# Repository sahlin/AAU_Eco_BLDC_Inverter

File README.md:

# AAU_Eco_BLDC_Inverter
Aalborg University BLDC control system for Shell EcoMarathon

This hardware achieved a second place in the efficiency competition Shell Ecomarathon Europe 2019 on a special designed hydrogen fueled eco racer car. The car was built by students at Aalborg University - Department of Energy Technology. We achieved a result of 214.27 km/m3 H2 (which is about 620 km/l 95 octane equivalent) and the motor system was a Grundfos PMSM motor and is rated at 2000 RPM, 2 Nm, 10.8V og 38A , but we are pushing it to 60A and 2500 RPM!

It's effectiveness with inverter included is best at 2000+ RPM and >1 Nm (90%), which put it at for our entire run (except for acceleration).

The initial work was done by the VESC Project. https://vesc-project.com/

Hardware is licensed under the Creative Commons Attribution-ShareAlike 4.0 International License. To view a copy of this license, visit http://creativecommons.org/licenses/by-sa/4.0/.

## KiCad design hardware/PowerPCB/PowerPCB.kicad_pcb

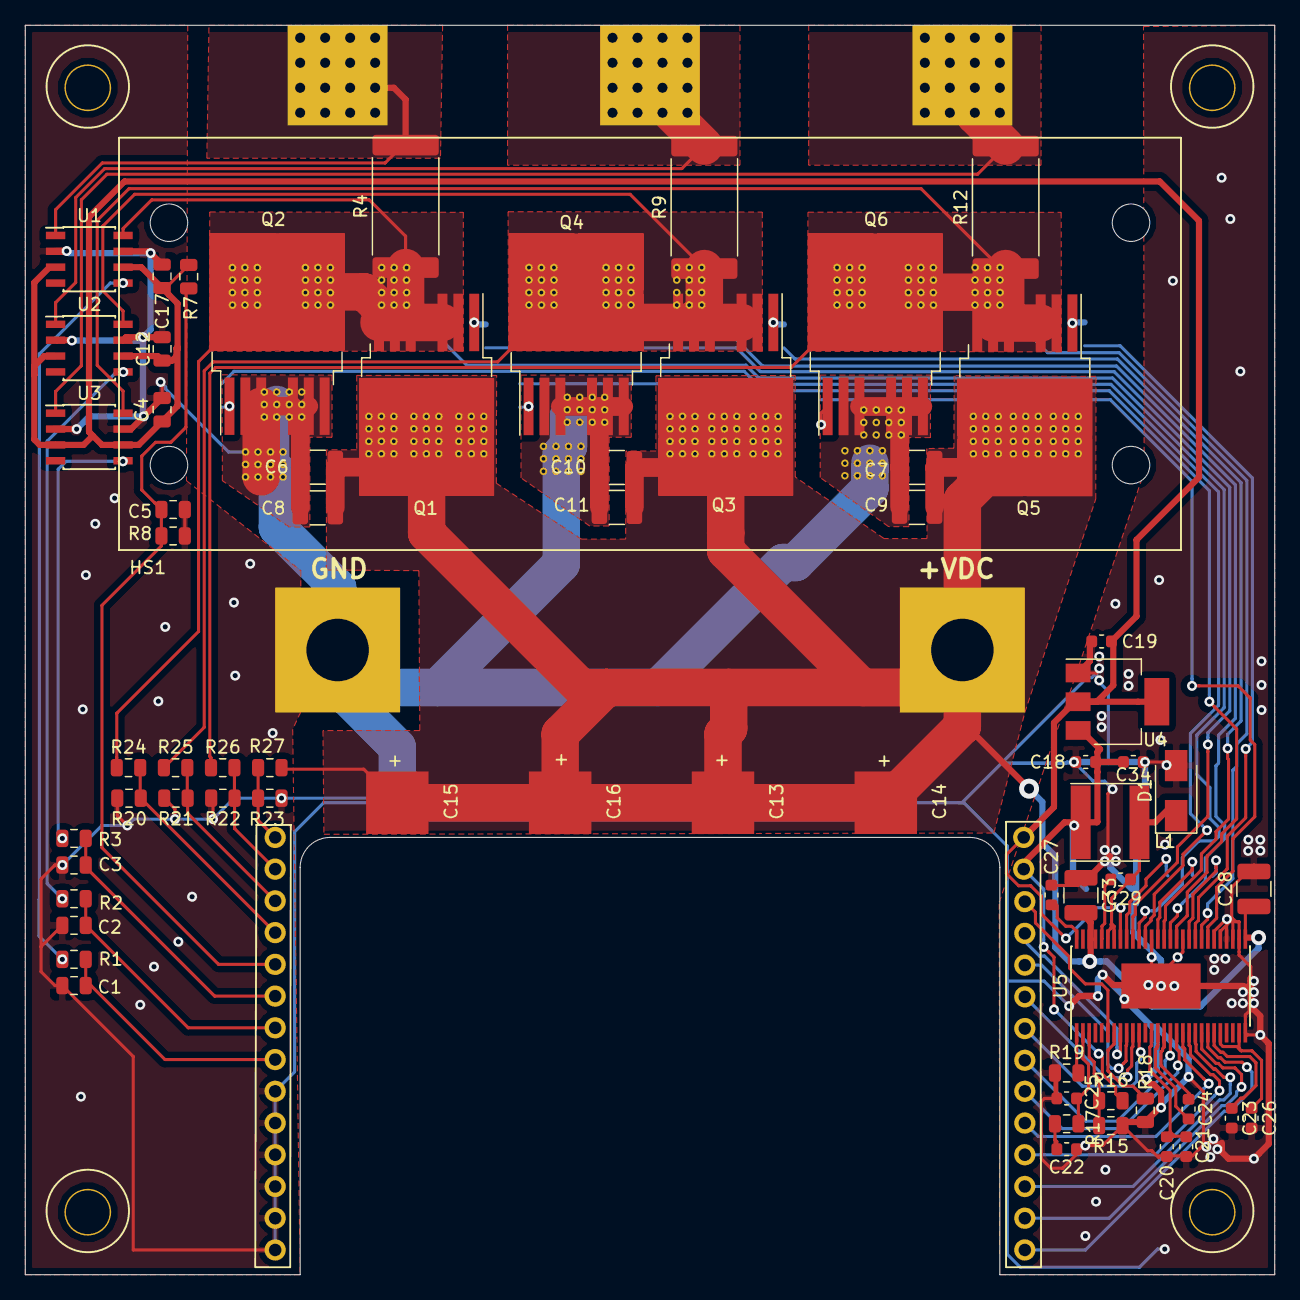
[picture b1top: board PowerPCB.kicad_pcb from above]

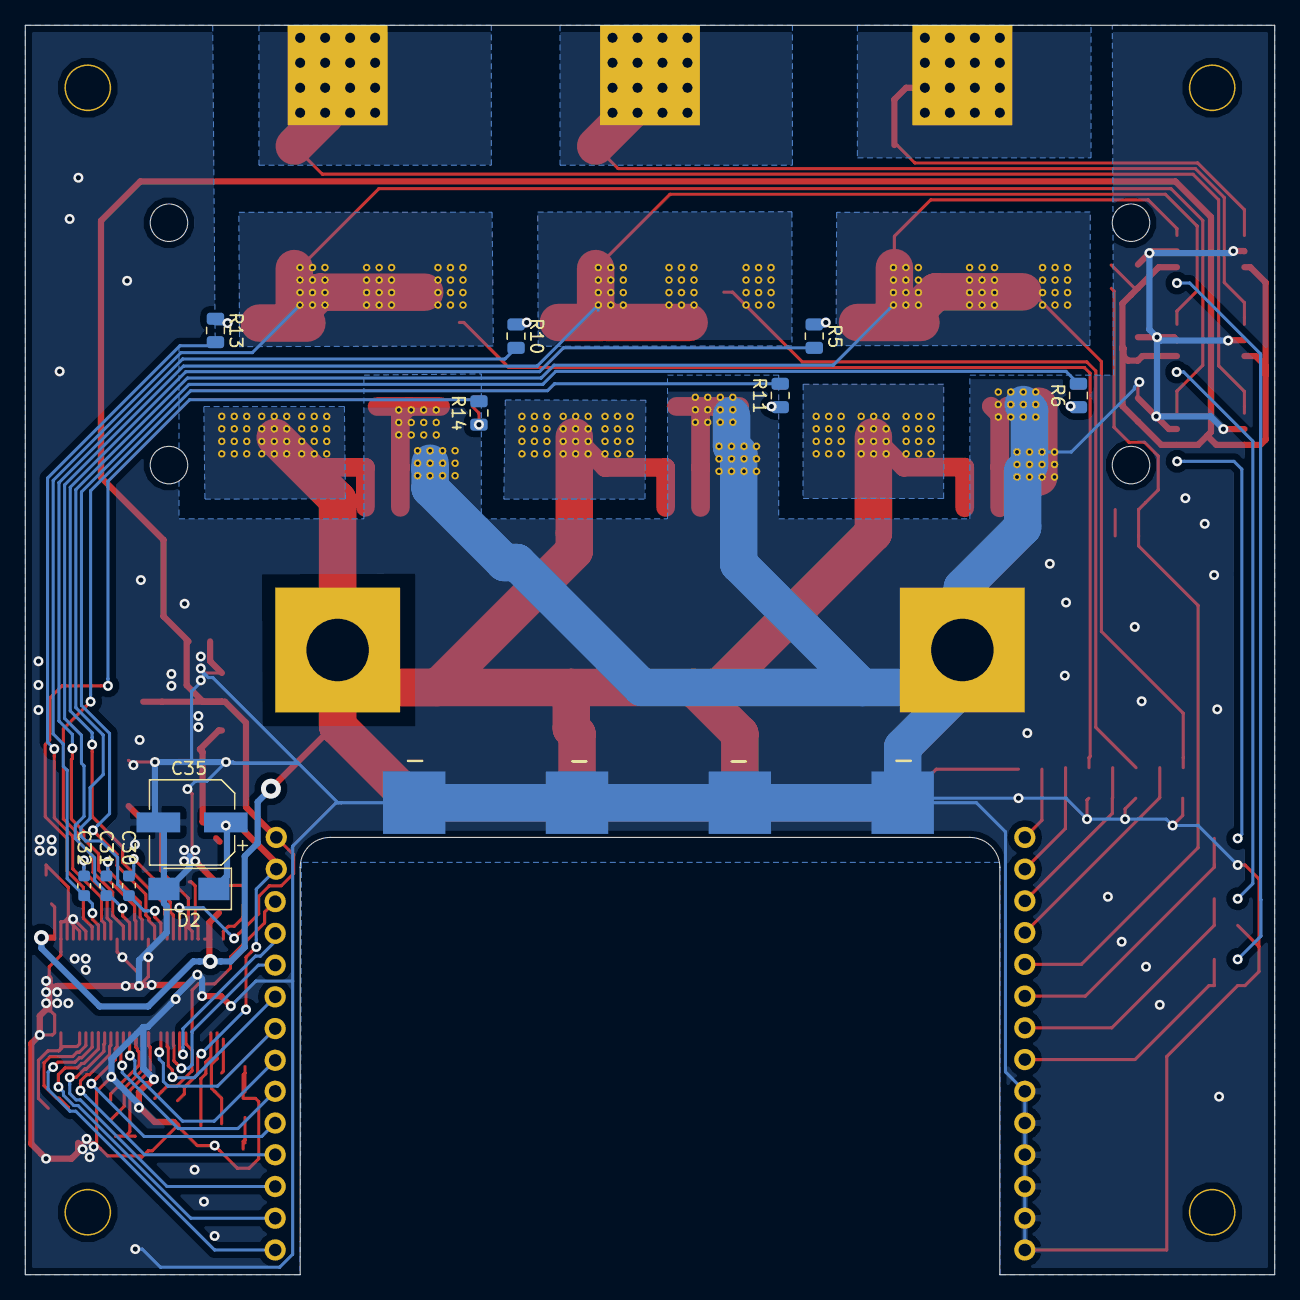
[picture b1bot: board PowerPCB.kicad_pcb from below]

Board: 2 copper layers, 100.0 x 100.0 mm, 111 parts (11 on the bottom side), 61 nets.

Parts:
C1, C2, C3: 4.7nF; C_0805_2012Metric
C4, C12, C17: 100nF; C_0805_2012Metric
C5: 2.2uF; C_0805_2012Metric
C6, C7, C8, C9, C10, C11, C28, C33: 4.7uF 100V; C_1210_3225Metric
C13, C14, C15, C16: EEUFC1J681L; CAP_inverter
C18, C19, C29: 100nF; C_0603_1608Metric
C20, C21, C23, C26, C34: 2.2uF; C_0603_1608Metric
C22: 6.8nF; C_0603_1608Metric
C24: 22nF; C_0603_1608Metric
C25: 120pF; C_0603_1608Metric
C27: 15nF; C_0603_1608Metric
C30, C31, C32: 220nF; C_0603_1608Metric
C35: 68uF; CP_Elec_6.3x5.7
D1: B360A-13-F; D_SMA
D2: SMAJ5.0A; D_SMA
HS1: Heatsink; HeatSink
J1: InverterConn
J2: PH_A; BulletConnector
J3: VDC; 5mmWireConn
J4: PH_B; BulletConnector
J5: PH_C; BulletConnector
J6: GND; 5mmWireConn
J7, J8, J9, J10: Conn_01x01; Spacer
L1: L; L_Taiyo-Yuden_NR-60xx
Q1, Q2, Q3, Q4, Q5, Q6: IPB010N06N; TO-263-6
R1, R2, R3: 100; R_0805_2012Metric
R4, R9, R12: Shunt 0.0002; R_4020_10251Metric_Pad1.65x5.30mm_HandSolder
R5, R6, R10, R11, R13, R14: 6.8; R_0805_2012Metric
R7: 10k NTC; R_0805_2012Metric
R8, R18: 10k; R_0805_2012Metric
R15: 3.3k; R_0805_2012Metric
R16: 18k; R_0805_2012Metric
R17: 15k; R_0805_2012Metric
R19: 220k; R_0805_2012Metric
R20, R21, R22, R23: 2.2k; R_0805_2012Metric
R24, R25, R26, R27: 39k; R_0805_2012Metric
U1, U2, U3: INA282; SOIC-8_3.9x4.9mm_P1.27mm
U4: TS1117BCW33; SOT-223-3_TabPin2
U5: DRV8301; HTSSOP-56-1EP_6.1x14mm_P0.5mm_EP3.61x6.35mm
Via1, Via2, Via3, Via4, Via5, Via6, Via7, Via8, Via9, Via10, Via11, Via12, Via13, Via14, Via15, Via16, Via17, Via18, Via19, Via20, Via21, Via22, Via23, Via24: Via_array

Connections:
+5V: C18.1, C34.1, C35.1, D2.1, J1.27, L1.1, R16.2, U4.3
+VDC: C6.2, C7.1, C8.1, C9.1, C10.1, C11.1, C13.1, C14.1, C15.1, C16.1, C28.1, C33.2, J3.1, Q1.D, Q3.D, Q5.D, R27.1, U5.29, U5.53, U5.54, Via13.1, Via14.1, Via15.1, Via16.1, Via17.1, Via18.1, Via19.1, Via20.1, Via21.1
/CS: J1.25, U5.8
/CURR_A: C1.1, J1.8, R1.2
/CURR_B: C2.1, J1.7, R2.2
/CURR_C: C3.1, J1.6, R3.2
/DRV8301/AVDD: C26.1, U5.24, U5.27
/DRV8301/BST_BK: C29.2, U5.52
/DRV8301/COMP: C25.2, R17.2, U5.2
/DRV8301/CP1: C24.1, U5.14
/DRV8301/CP2: C24.2, U5.15
/DRV8301/DTC: R18.1, U5.7
/DRV8301/DVDD: C23.1, U5.23
/DRV8301/GH_A: R5.2, U5.47
/DRV8301/GH_B: R10.2, U5.42
/DRV8301/GH_C: R13.2, U5.37
/DRV8301/GL_A: R6.2, U5.45
/DRV8301/GL_B: R11.2, U5.40
/DRV8301/GL_C: R14.2, U5.35
/DRV8301/GVDD: C20.2, C21.2, U5.13
/DRV8301/PH: C29.1, D1.1, L1.2, U5.50, U5.51
/DRV8301/RT_CLK: R19.2, U5.1
/DRV8301/SH_A: C30.1, Q1.S, Q2.D, R4.1, R24.1, U1.8, U5.46, Via1.1, Via2.1, Via3.1
/DRV8301/SH_B: C31.1, Q3.S, Q4.D, R9.1, R25.1, U2.8, U5.41, Via5.1, Via6.1, Via7.1
/DRV8301/SH_C: C32.1, Q5.S, Q6.D, R12.1, R26.1, U3.8, U5.36, Via9.1, Via10.1, Via11.1
/DRV8301/VSENSE: R15.2, R16.1, U5.3
/EN_GATE: J1.21, U5.16
/FAULT: J1.26, U5.6
/INH_A: J1.20, U5.17
/INH_B: J1.18, U5.19
/INH_C: J1.16, U5.21
/INL_A: J1.19, U5.18
/INL_B: J1.17, U5.20
/INL_C: J1.15, U5.22
/Inverter/C_A: R1.1, U1.5
/Inverter/C_B: R2.1, U2.5
/Inverter/C_C: R3.1, U3.5
/SCLK: J1.22, U5.11
/SDI: J1.24, U5.9
/SDO: J1.23, U5.10
/SENS_A: J1.4, R20.1, R24.2
/SENS_B: J1.3, R21.1, R25.2
/SENS_C: J1.2, R22.1, R26.2
/SENS_SUPPLY: J1.1, R23.1, R27.2
/TEMP: C5.1, J1.5, R7.2, R8.1
GND: C1.2, C2.2, C3.2, C4.2, C5.2, C6.1, C7.2, C8.2, C9.2, C10.2, C11.2, C12.2, C13.2, C14.2, C15.2, C16.2, C17.2, C18.2, C19.2, C20.1, C21.1, C22.1, C23.2, C25.1, C26.2, C27.1, C28.2, C33.1, C34.2, C35.2, D1.2, D2.2, J1.9, J1.10, J1.11, J1.12, J1.13, J1.14, J6.1, Q2.S, Q4.S, Q6.S, R8.2, R15.1, R18.2, R19.1, R20.2, R21.2, R22.2, R23.2, U1.2, U1.7, U2.2, U2.7, U3.2, U3.7, U4.1, U5.28, U5.30, U5.31, U5.32, U5.33, U5.34, U5.39, U5.44, U5.57, Via4.1, Via8.1, Via12.1, Via22.1, Via23.1, Via24.1
unnamed: C22.2, R17.1
unnamed: C27.2, U5.56
unnamed: C30.2, U5.48
unnamed: C31.2, U5.43
unnamed: C32.2, U5.38
unnamed: J2.1, R4.2, U1.1
unnamed: J4.1, R9.2, U2.1
unnamed: J5.1, R12.2, U3.1
unnamed: Q1.G, R5.1
unnamed: Q2.G, R6.1
unnamed: Q3.G, R10.1
unnamed: Q4.G, R11.1
unnamed: Q5.G, R13.1
unnamed: Q6.G, R14.1
VCC: C4.1, C12.1, C17.1, C19.1, J1.28, R7.1, U1.3, U1.6, U2.3, U2.6, U3.3, U3.6, U4.2, U5.49

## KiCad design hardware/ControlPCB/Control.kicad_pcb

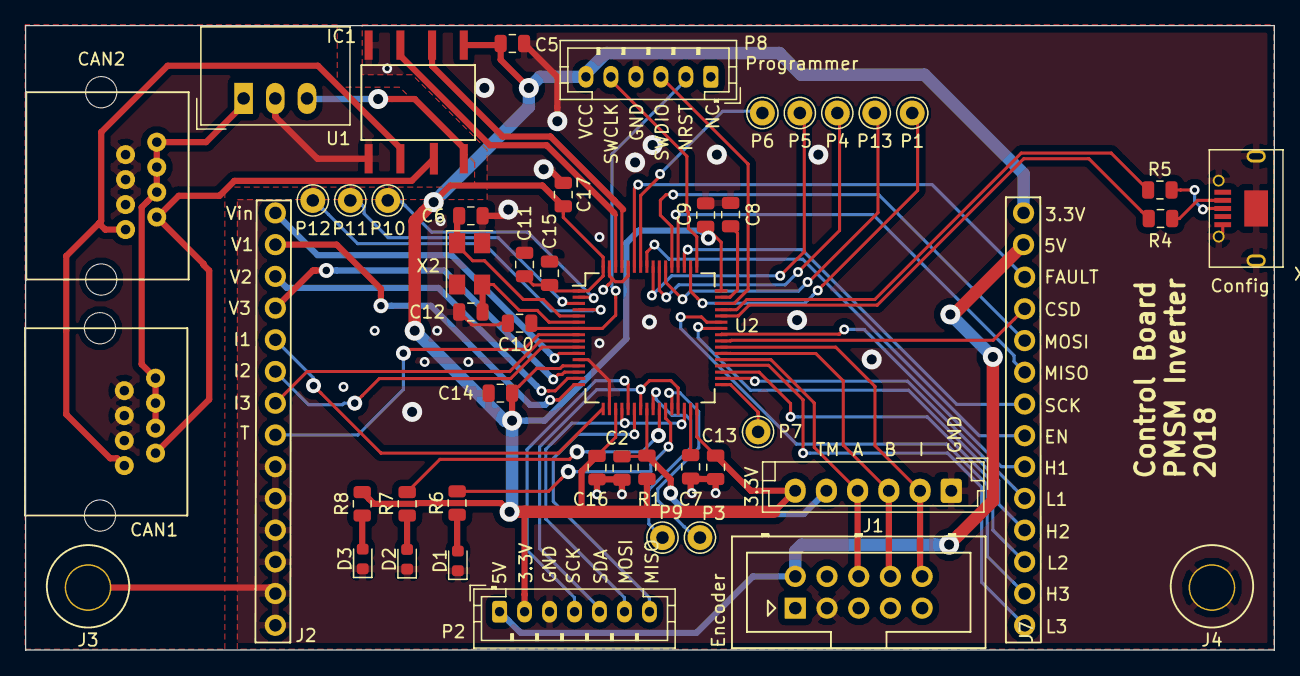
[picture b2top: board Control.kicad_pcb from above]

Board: 2 copper layers, 100.0 x 50.0 mm, 48 parts (0 on the bottom side), 65 nets.

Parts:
C2, C10: 100n; C_0805_2012Metric
C5, C7, C8, C9, C11, C13, C14, C15, C16, C17: 2.2u; C_0805_2012Metric
C6, C12: 15p; C_0805_2012Metric
CAN1, CAN2: RJ45CAN; RJ45
D1: RED; LED_0603_1608Metric
D2: GREEN; LED_0603_1608Metric
D3: LED; LED_0603_1608Metric
IC1: ISO1050
J1: Conn_01x06; JST_EH_B06B-EH-A_1x06_P2.50mm_Vertical
J2: InverterConn
J3, J4: Mounting; Spacer
J7: Quadrature Encoder; Multicomp_MC9A12-1034_2x05_P2.54mm_Vertical
P1, P3, P4, P5, P6, P7, P9, P10, P11, P12, P13: CONN_1; Pin_D1.0mm_L10.0mm
P2: PWR_COMM; JST_PH_B7B-PH-K_1x07_P2.00mm_Vertical
P8: SWD; JST_PH_B6B-PH-K_1x06_P2.00mm_Vertical
R1: 10k; R_0805_2012Metric
R4, R5: 22R; R_0805_2012Metric
R6, R7: 100R; R_0805_2012Metric
R8: 2k2; R_0805_2012Metric
U1: TSR_1-2450; Converter_DCDC_TRACO_TSR-1_THT
U2: STM32F405RGTx; LQFP-64_10x10mm_P0.5mm
X1: MINI-USB-SHIELD-32005-201; USB_Micro-AB-MOLEX-47590-0001
X2: 8MHz 10ppm; Crystal_SMD_5032-4Pin_5.0x3.2mm

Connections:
+5V: J2.27, J7.2, P2.1
+12V: CAN1.3, CAN1.5, CAN1.7, CAN2.3, CAN2.5, CAN2.7, U1.1
/A+: J1.4, J7.6, U2.37
/ADC_TEMP: J2.5, U2.17
/B+: J1.3, J7.8, U2.38
/CAN bus transceiver/5V_CAN: IC1.8, U1.3
/CAN bus transceiver/CANH: CAN1.1, CAN2.1, IC1.7
/CAN bus transceiver/CANL: CAN1.2, CAN2.2, IC1.6
/CAN bus transceiver/CAN_RX: IC1.2, U2.61
/CAN bus transceiver/CAN_TX: IC1.3, U2.62
/Current1: J2.8, U2.8
/Current2: J2.7, U2.9
/Current3: J2.6, U2.10
/D+: R5.2, X1.3
/D-: R4.2, X1.2
/EN_GATE: J2.21, U2.57
/FAULT: J2.26, U2.59
/GreenLED: D2.2, R7.1
/H1: J2.20, U2.41
/H2: J2.18, U2.42
/H3: J2.16, U2.43
/I+: J1.2, J7.10, U2.39
/L1: J2.19, U2.34
/L2: J2.17, U2.35
/L3: J2.15, U2.36
/MCU/LED_GREEN: R7.2, U2.26
/MCU/LED_RED: R6.2, U2.27
/MCU/TEMP_MOTOR: C2.2, J1.5, R1.1, U2.24
/MCU/USB_DM: R4.1, U2.44
/MCU/USB_DP: R5.1, U2.45
/MISO_RX_SCL: P2.7, U2.22
/PA15: P1.1, U2.50
/PB2: P3.1, U2.28
/PB3: P4.1, U2.55
/PB4: P5.1, U2.56
/PB6: P6.1, U2.58
/PB12: P7.1, U2.33
/PC5: P9.1, U2.25
/PC13: P10.1, U2.2
/PC14: P11.1, U2.3
/PC15: P12.1, U2.4
/PD2: P13.1, U2.54
/RX_SCL_MOSI: P2.6, U2.20, U2.30
/RedLED: D1.2, R6.1
/SCK_ADC_EXT: P2.4, U2.21
/SPI3_CSD: J2.25, U2.40
/SPI3_MISO: J2.23, U2.52
/SPI3_MOSI: J2.24, U2.53
/SPI3_SCK: J2.22, U2.51
/Supply_SENS: J2.1, U2.11
/TX_SDA: P2.5, U2.23, U2.29
/Voltage1: J2.4, U2.14
/Voltage2: J2.3, U2.15
/Voltage3: J2.2, U2.16
GND: C2.1, C5.2, C6.2, C7.2, C8.2, C9.1, C10.1, C11.1, C12.2, C13.1, C14.1, C15.1, C16.1, C17.1, D1.1, D2.1, D3.1, IC1.4, J1.1, J2.9, J2.10, J2.11, J2.12, J2.13, J2.14, J3.1, J4.1, J7.3, P2.3, P8.4, U2.12, U2.18, U2.60, U2.63, X1.5, X1.6, X2.2, X2.4
GNDCAN: CAN1.4, CAN1.6, CAN1.8, CAN2.4, CAN2.6, CAN2.8, IC1.5, U1.2
NRST: C10.2, P8.2, U2.7
unnamed: C6.1, U2.5, X2.1
unnamed: C7.1, U2.31
unnamed: C8.1, U2.47
unnamed: C12.1, U2.6, X2.3
unnamed: D3.2, R8.1
SWCLK: P8.5, U2.49
SWDIO: P8.3, U2.46
VCC: C5.1, C9.2, C11.2, C13.2, C14.2, C15.2, C16.2, C17.2, IC1.1, J1.6, J2.28, P2.2, P8.6, R1.2, R8.2, U2.1, U2.13, U2.19, U2.32, U2.48, U2.64

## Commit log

2019-07-04 First hardware commit
2019-07-04 Added images
2019-07-04 Update README.md
    Added images
